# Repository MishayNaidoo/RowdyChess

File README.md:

# RowdyChess
Building a rowdy chessboard
Hello

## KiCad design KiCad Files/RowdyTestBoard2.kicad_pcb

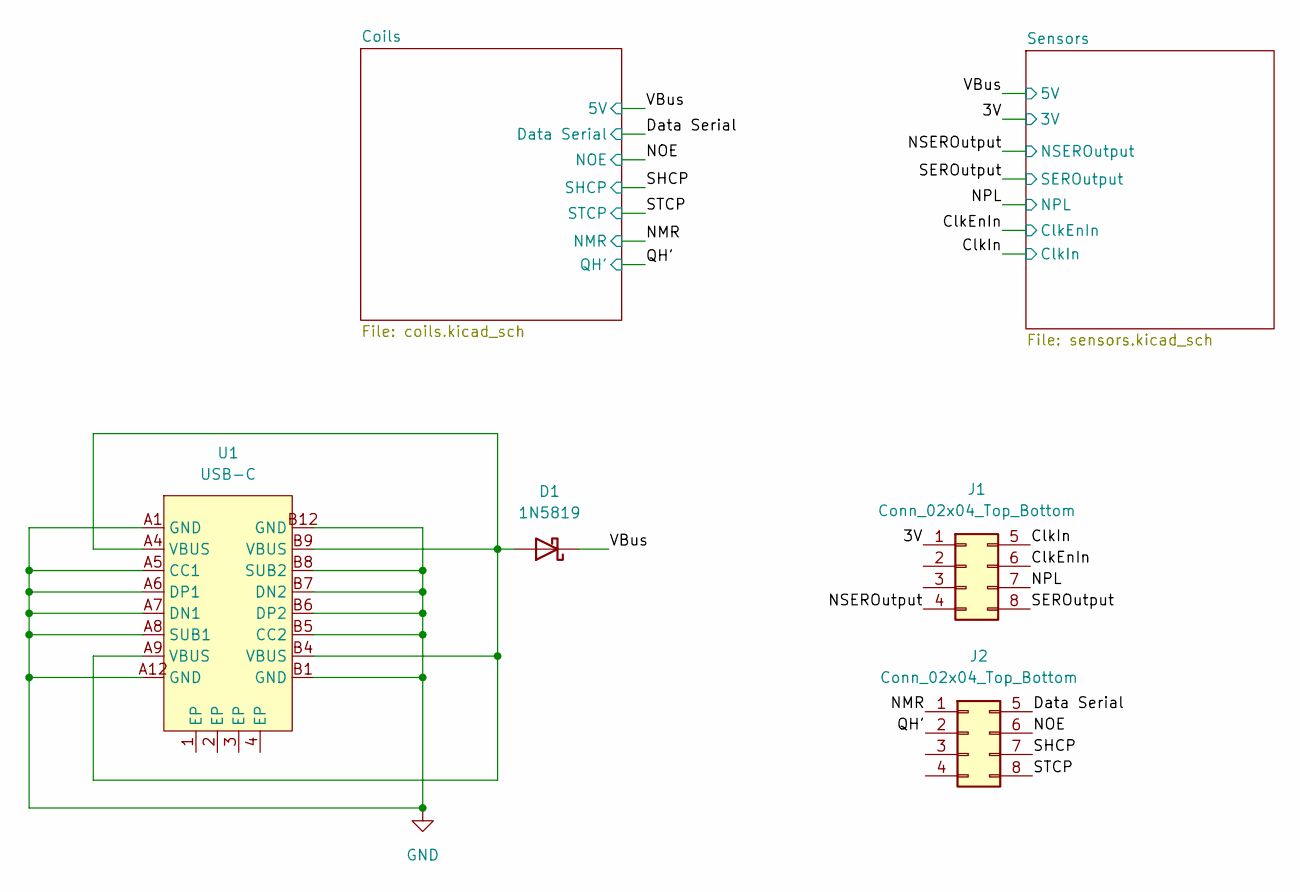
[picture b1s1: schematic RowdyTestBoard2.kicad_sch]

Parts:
D1: 1N5819; D_SOD-323F; JLC Part Number C2128
J1, J2: Conn_02x04_Top_Bottom; PinHeader_2x04_P2.54mm_Vertical_SMD
U1: USB-C; USB-C-SMD_KH-TYPE-C-16P; JLC Part Number C709357

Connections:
/3V: J1.1; also elsewhere on the board
/ClkEnIn: J1.6; also elsewhere on the board
/ClkIn: J1.5; also elsewhere on the board
/Data Serial: J2.5; also elsewhere on the board
/NMR: J2.1; also elsewhere on the board
/NOE: J2.6; also elsewhere on the board
/NPL: J1.7; also elsewhere on the board
/NSEROutput: J1.4; also elsewhere on the board
/QH': J2.2; also elsewhere on the board
/SEROutput: J1.8; also elsewhere on the board
/SHCP: J2.7; also elsewhere on the board
/STCP: J2.8; also elsewhere on the board
/VBus: D1.1 (K); also elsewhere on the board
GND: U1.A1 (GND), U1.A5 (CC1), U1.A6 (DP1), U1.A7 (DN1), U1.A8 (SUB1), U1.A12 (GND), U1.B1 (GND), U1.B5 (CC2), U1.B6 (DP2), U1.B7 (DN2), U1.B8 (SUB2), U1.B12 (GND); also elsewhere on the board
unnamed: D1.2 (A), U1.A4 (VBUS), U1.A9 (VBUS), U1.B4 (VBUS), U1.B9 (VBUS)

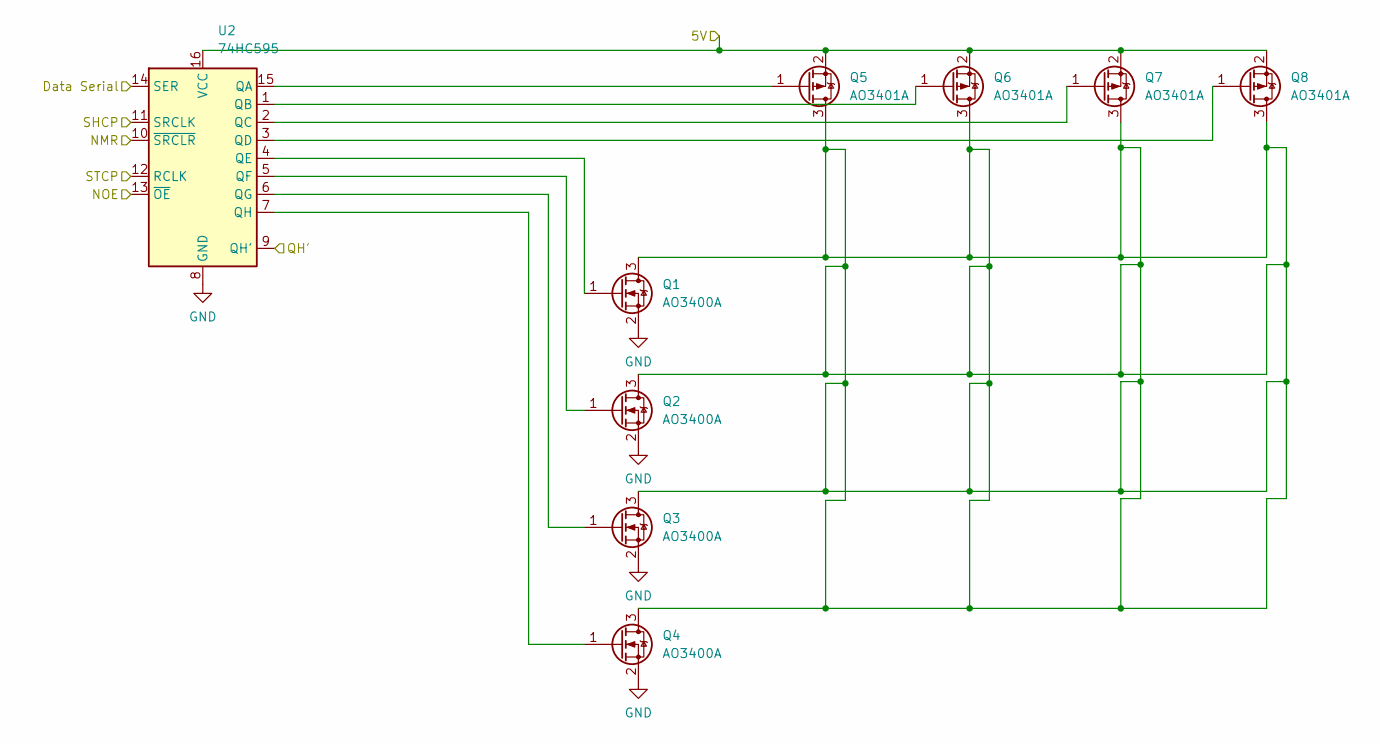
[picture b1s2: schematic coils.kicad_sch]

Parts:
Q1, Q2, Q3, Q4: AO3400A; SOT-23; JLC Part Number C20917
Q5, Q6, Q7, Q8: AO3401A; SOT-23; JLC Part Number C15127
U2: 74HC595; SO16; JLC Part Number C5947

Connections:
/Data Serial: U2.14 (SER); also elsewhere on the board
/NMR: U2.10 (~SRCLR); also elsewhere on the board
/NOE: U2.13 (~OE); also elsewhere on the board
/QH': U2.9 (QH'); also elsewhere on the board
/SHCP: U2.11 (SRCLK); also elsewhere on the board
/STCP: U2.12 (RCLK); also elsewhere on the board
/VBus: Q5.2 (S), Q6.2 (S), Q7.2 (S), Q8.2 (S), U2.16 (VCC); also elsewhere on the board
GND: Q1.2 (S), Q2.2 (S), Q3.2 (S), Q4.2 (S), U2.8 (GND); also elsewhere on the board
unnamed: Q1.1 (G), U2.4 (QE)
unnamed: Q1.3 (D), Q2.3 (D), Q3.3 (D), Q4.3 (D), Q5.3 (D), Q6.3 (D), Q7.3 (D), Q8.3 (D)
unnamed: Q2.1 (G), U2.5 (QF)
unnamed: Q3.1 (G), U2.6 (QG)
unnamed: Q4.1 (G), U2.7 (QH)
unnamed: Q5.1 (G), U2.15 (QA)
unnamed: Q6.1 (G), U2.1 (QB)
unnamed: Q7.1 (G), U2.2 (QC)
unnamed: Q8.1 (G), U2.3 (QD)

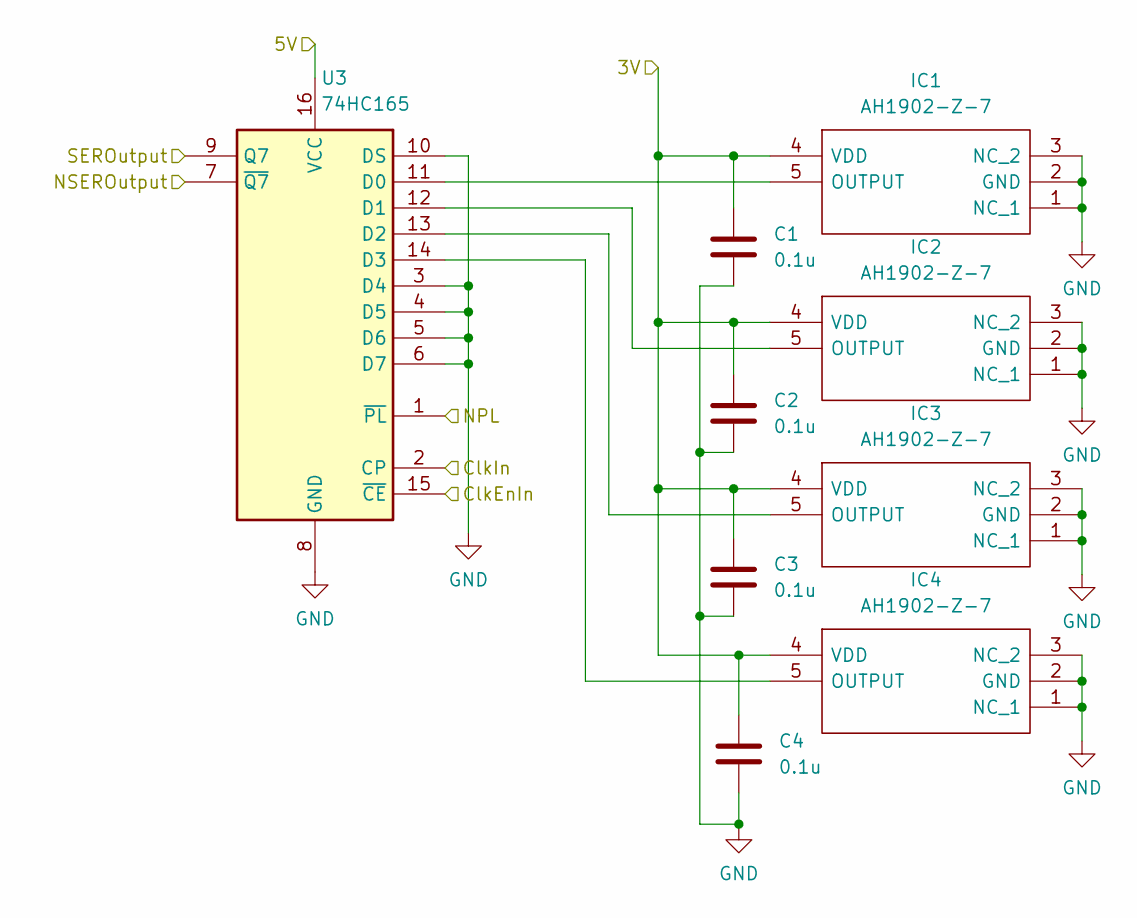
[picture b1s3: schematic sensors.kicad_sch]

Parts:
C1, C2, C3, C4: 0.1u; C_0402_1005Metric; JLC Part Number C1525
IC1, IC2, IC3, IC4: AH1902-Z-7; AH1902Z7; Manufacturer_Part_Number AH1902-Z-7; Mouser Part Number 621-AH1902-Z-7
U3: 74HC165; SO-16; JLC Part Number C5613

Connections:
/3V: C1.1, C2.1, C3.1, C4.1, IC1.4 (VDD), IC2.4 (VDD), IC3.4 (VDD), IC4.4 (VDD); also elsewhere on the board
/ClkEnIn: U3.15 (~CE); also elsewhere on the board
/ClkIn: U3.2 (CP); also elsewhere on the board
/NPL: U3.1 (~PL); also elsewhere on the board
/NSEROutput: U3.7 (~Q7); also elsewhere on the board
/SEROutput: U3.9 (Q7); also elsewhere on the board
/VBus: U3.16 (VCC); also elsewhere on the board
GND: C1.2, C2.2, C3.2, C4.2, IC1.1 (NC_1), IC1.2 (GND), IC1.3 (NC_2), IC2.1 (NC_1), IC2.2 (GND), IC2.3 (NC_2), IC3.1 (NC_1), IC3.2 (GND), IC3.3 (NC_2), IC4.1 (NC_1), IC4.2 (GND), IC4.3 (NC_2), U3.3 (D4), U3.4 (D5), U3.5 (D6), U3.6 (D7), U3.8 (GND), U3.10 (DS); also elsewhere on the board
unnamed: IC1.5 (OUTPUT), U3.11 (D0)
unnamed: IC2.5 (OUTPUT), U3.12 (D1)
unnamed: IC3.5 (OUTPUT), U3.13 (D2)
unnamed: IC4.5 (OUTPUT), U3.14 (D3)

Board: 4 copper layers, 22 parts (0 on the bottom side), 28 nets, no tracks yet.

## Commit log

2022-06-19 New Kicad files
2022-06-19 Neat
2022-06-19 Not sure
2022-06-19 Hierarchial
2022-06-19 More mosfets
2022-06-19 Footprints
2022-06-19 Datsheets
2022-06-19 Sure
2022-06-19 Coils updated
2022-06-19 Coils done
2022-06-19 Switch
2022-06-19 hello
2022-06-19 added Symbol
2022-06-19 hall1
2022-06-19 Hall sensors mux
2022-06-20 Sensors Done
2022-06-20 Startpcb
2022-06-20 Added footprints
2022-06-20 Added USB-C Symbol
2022-06-20 More footprints
2022-06-20 Settings
2022-06-20 Pcb2
2022-06-20 diode
2022-06-20 Big coils
2022-06-20 Pull down resistors
2022-06-20 Resistors
2022-06-20 Business
2022-06-20 Coils business
2022-06-21 Big saucy business
2022-06-21 Big coils baby
2022-06-21 Mosfet crazy town
2022-06-22 Wiring sauce
2022-06-22 Mosfets to coils pt 1
2022-06-22 Mosfets to coils pt 2
2022-06-22 Mosfet touch up
2022-06-22 ABsolute mastery
2022-06-22 Raw sauce vias
2022-06-22 Wiring monster
2022-06-22 Long mosfets
2022-06-22 Raw sauce
2022-06-22 Rowdy times
2022-06-22 DONE ROUTING
2022-06-23 Mosfets to coils 1 pt1
2022-06-23 Mosfets to coils 1 pt2
2022-06-23 Mosfets to coils 1 pt3
2022-06-23 Saucy wiring pt1
2022-06-23 Saucy wiring pt2
2022-06-23 Saucy wiring pt3
2022-06-23 Saucy wiring pt4 i think
2022-06-23 Saucy wiring pt5 ish
2022-06-23 ALmost there
2022-06-23 Almost there pt2
2022-06-23 ALmost there pt 3
2022-06-23 More routing madness
2022-06-23 Fuxk my life pt 1
2022-06-23 Fuxk my life pt 2
2022-06-23 Fuxk my life pt3
2022-06-24 Mosfet rails done pt1
2022-06-24 Mosfet rails done pt2
2022-06-24 Mosfet rails done pt3
2022-06-24 Mosfet rails done pt5
2022-06-24 Mosfet rails done pt6
2022-06-24 Mosfet rails done pt7
2022-06-24 Mosfet rails done pt8
2022-06-24 pt 9 I think
2022-06-24 Big push
2022-06-24 Big push pt 2
2022-06-26 Routing done pt 1
2022-06-26 Done routing pt 2
2022-06-26 Final pt 1
2022-06-26 Final pt 2
2022-06-27 Changed 90 degree traces
2022-06-27 Generated JLC PCB Files
2022-07-02 Word doc added
2022-07-04 New Hall Sensors
2022-07-04 New hall sensors on pcb
2022-07-05 David FFS Merge pt 1
2022-07-05 David FFS Merge pt 2
2022-07-05 David FFS Merge pt 3
2022-07-05 David FFS Merge pt 4
2022-07-05 David FFS Merge pt 5
2022-07-05 David FFS Merge pt 6
2022-07-05 David FFS Merge pt 7
2022-07-05 David FFS Merge pt 8
2022-07-05 David FFS Merge pt 9
2022-07-06 Not sure what this is
2022-07-06 Generated Gerbers
2022-07-13 Update report
